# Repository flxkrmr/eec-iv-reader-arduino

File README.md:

# Arduino EEC IV Reader

Arduino implementation of the DCL-Protocol to communicate with Ford EEC-IV ECUs.

Please check out the Wiki for more information.

This is currently a work in progress and not completely working. Use at your own risk!

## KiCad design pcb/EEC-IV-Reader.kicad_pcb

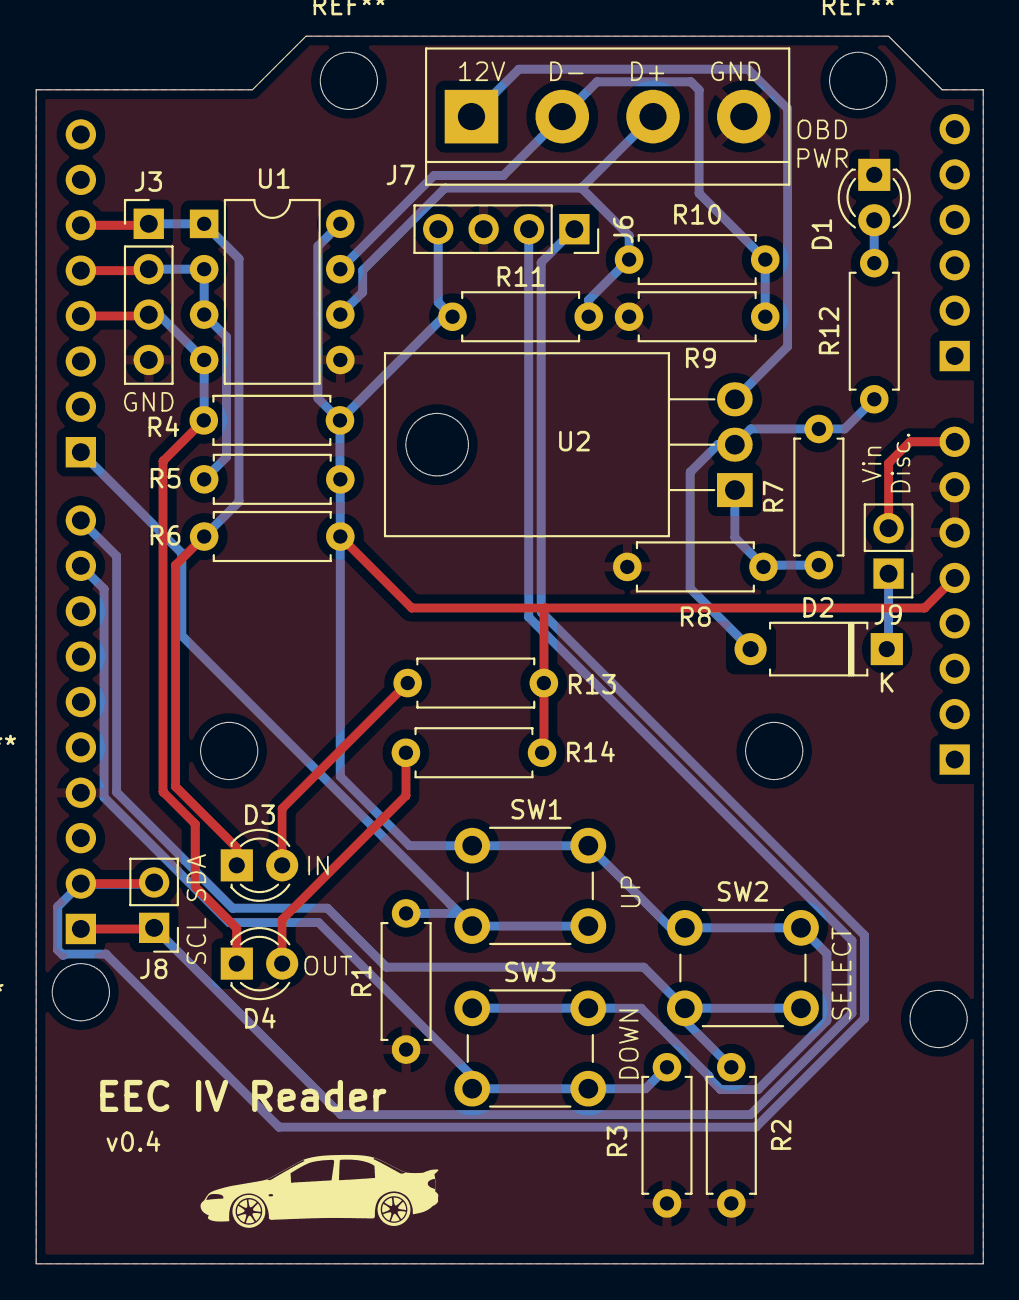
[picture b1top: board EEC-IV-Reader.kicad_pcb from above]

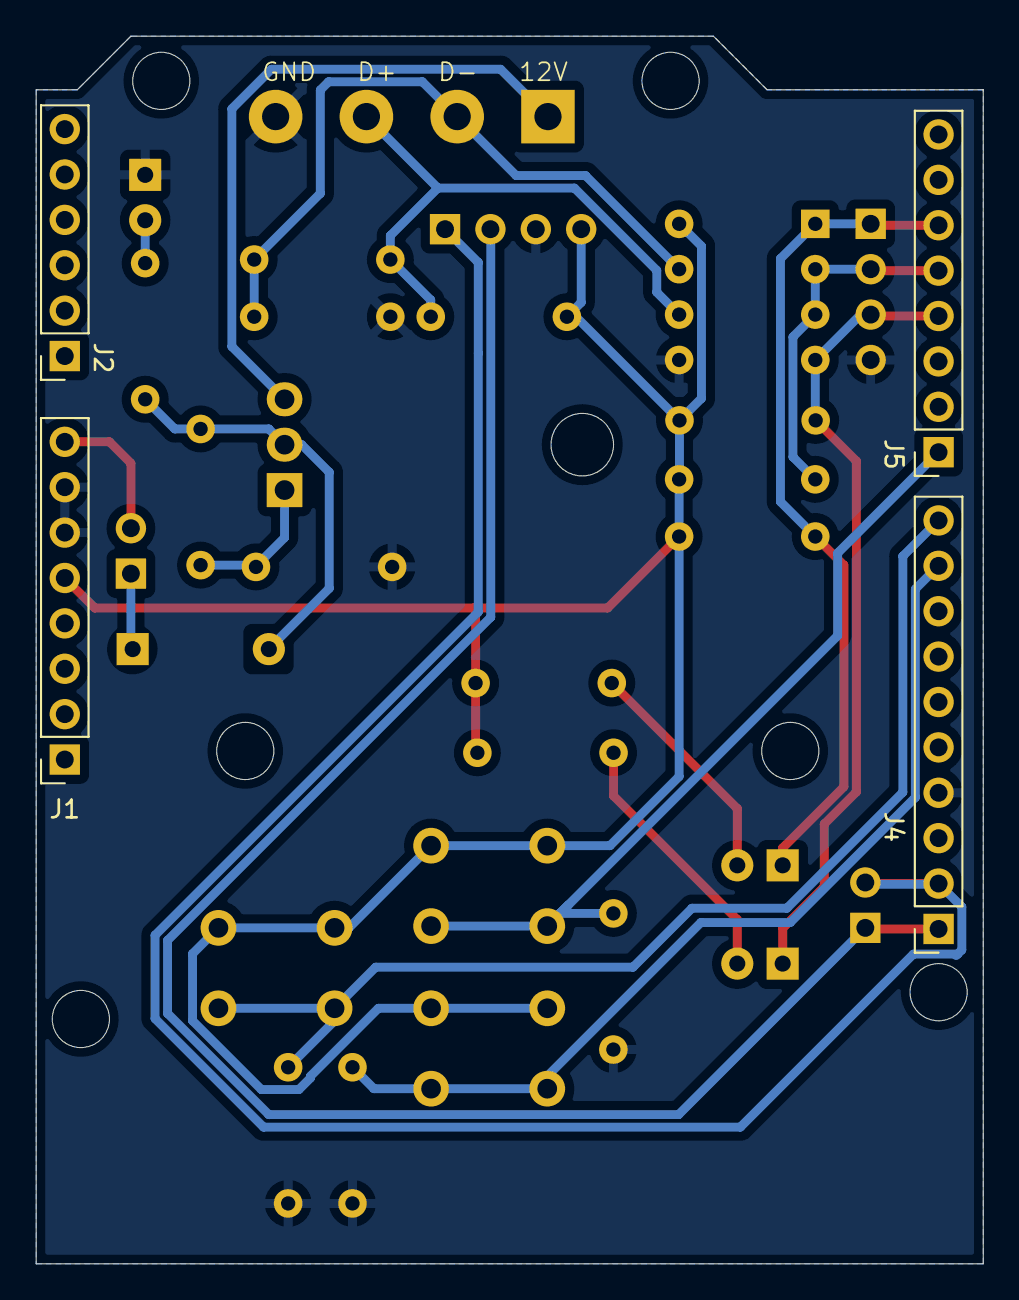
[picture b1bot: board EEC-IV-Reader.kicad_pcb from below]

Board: 2 copper layers, 53.0 x 68.7 mm, 32 parts (4 on the bottom side), 20 nets.

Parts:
D1, D3, D4: LED; LED_D3.0mm
D2: D_Schottky; D_A-405_P7.62mm_Horizontal
J1: ARDUINO_1; PinSocket_1x08_P2.54mm_Vertical
J2: ARDUINO_2; PinSocket_1x06_P2.54mm_Vertical
J3: RS_485_DEBUG; PinHeader_1x04_P2.54mm_Vertical
J4: ARDUINO_3; PinSocket_1x10_P2.54mm_Vertical
J5: ARDUINO_4; PinSocket_1x08_P2.54mm_Vertical
J6: DISPLAY; PinSocket_1x04_P2.54mm_Vertical
J7: OBD; TerminalBlock_bornier-4_P5.08mm
J8: I2C_DEBUG; PinHeader_1x02_P2.54mm_Vertical
J9: Vin_disconnect; PinHeader_1x02_P2.54mm_Vertical
R1, R2, R3, R4, R5, R6: 10k; R_Axial_DIN0207_L6.3mm_D2.5mm_P7.62mm_Horizontal
R7: 240; R_Axial_DIN0207_L6.3mm_D2.5mm_P7.62mm_Horizontal
R8: 1k3; R_Axial_DIN0207_L6.3mm_D2.5mm_P7.62mm_Horizontal
R9, R11: 20k; R_Axial_DIN0207_L6.3mm_D2.5mm_P7.62mm_Horizontal
R10: 120; R_Axial_DIN0207_L6.3mm_D2.5mm_P7.62mm_Horizontal
R12: 300; R_Axial_DIN0207_L6.3mm_D2.5mm_P7.62mm_Horizontal
R13, R14: 160; R_Axial_DIN0207_L6.3mm_D2.5mm_P7.62mm_Horizontal
SW1: BTN_UP; SW_PUSH_6mm_H4.3mm
SW2: BTN_SEL; SW_PUSH_6mm_H4.3mm
SW3: BTN_DOWN; SW_PUSH_6mm_H4.3mm
U1: MAX485E; DIP-8_W7.62mm
U2: LM317_TO-220; TO-220-3_Horizontal_TabDown

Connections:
2: D3.1 (K), J3.1, J5.6, R6.2, U1.1 (RO)
3: J3.2, J5.5, R5.2, U1.2 (~RE), U1.3 (DE)
4: D4.1 (K), J3.3, J5.4, R4.2, U1.4 (DI)
7: J5.1, R1.1, SW1.2
8: J4.10, R2.1, SW2.2
9: J4.9, R3.1, SW3.2
+5V: J1.5, J6.4, R4.1, R5.1, R6.1, R11.2, R13.1, R14.1, SW1.1, SW2.1, SW3.1, U1.8 (VCC)
+12V: J7.1, U2.3 (VI)
/8V: D2.1 (K), R7.1, R12.1, U2.2 (VO)
D+: J7.3, R10.2, R11.1, U1.6 (A)
D-: J7.2, R9.2, R10.1, U1.7 (B)
GND: D1.1 (K), J1.6, J1.7, J3.4, J4.4, J6.3, J7.4, R1.2, R2.2, R3.2, R8.2, R9.1, U1.5 (GND)
unnamed: D1.2 (A), R12.2
unnamed: D2.2 (A), J9.1
unnamed: D3.2 (A), R13.2
unnamed: D4.2 (A), R14.2
unnamed: R7.2, R8.1, U2.1 (ADJ)
SCL: J4.1, J6.2, J8.1
SDA: J4.2, J6.1, J8.2
VIN: J1.8, J9.2

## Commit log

2022-02-03 First working
2022-02-06 Log output for sync logic
2022-02-06 Logging sync message
2022-02-07 Removed docs from repo
2022-02-07 Add sync loop answers
2022-02-07 Move pointer increment
2022-02-07 Add gitignore
2022-02-08 Remove hacked SoftwareSerial
2022-02-10 Fix sync answer timing
2022-02-16 First baud change after sync
2022-02-16 Add state machine
2022-02-16 Somehow reads error code
2022-02-16 Switch fully to SoftwareSerial
2022-02-17 Printing 5 error codes to serial
2022-02-22 Added timeout and starting when sync loop is on
2022-02-22 Add todo list
2022-02-25 Rename all
2022-02-25 Refactor code
2022-02-25 Fix koeo
2022-02-26 Add .docs to gitignore
2022-02-26 Add readme
2022-02-26 Update ui
2022-02-26 Add comments to koeo
2022-03-05 Add button ui
2022-03-06 Move fault code to external class
2022-03-06 Move koeo to external class
2022-03-06 Add live data WIP
2022-03-06 Fix segmentation fault error
2022-03-20 WIP menu
2022-03-21 Add display gui
2022-04-04 Switch back to big class
2022-04-06 Switch to homemade menu
2022-04-06 Add koeo to ui
2022-04-06 Remove live data from ui
2022-04-11 Update TODO
2022-10-07 Add circuit board
2022-10-23 Fix pin out for proto board
2022-10-28 Port to platformio
2022-10-28 Remove submodules and add static files
2022-10-28 Fix git mess
2022-10-28 Invert KOEO menu
2022-10-28 Add basic unit test
2022-10-28 WIP: Implement fault code util with tests
2022-10-29 Implement fault code util with tests
2022-10-29 Fix string assertion
2022-10-29 Add convenience method
2022-10-30 Print readable message on fault code
2022-10-30 Remove usage of readable error codes
    Memory is too low.
2022-10-30 Improve board
2022-11-04 Rename modes
2022-11-04 Add start message timeout
2022-11-04 Get out of static message with up and down button
2022-11-06 Cleanup files
2022-12-30 Update PCB
2023-01-08 Stop on koeo code 000
2023-01-13 Update LED Labels and Diode direction
2023-01-13 Fix koeo for dynamic error number
2023-01-14 Fixing koeo again for only one error
2023-01-14 Add comments on koeo variables
2023-01-14 Add version
2023-01-20 Add terminal labels to backside
2023-01-20 Add bom
2023-01-20 Fix version
2023-01-20 Fix footprint
2023-01-20 Add step file
2023-01-20 Remove unused classes
2023-01-20 Improve variable size
2023-01-20 Increase version
2023-01-21 Memory improvement and warning cleanup
2023-01-26 Use OneButton Library
2023-01-26 Fix button setup
2023-01-26 Remove wire library
2023-01-26 Add small memory improvements
2023-01-27 Fix warning
2023-01-27 Add voltage divider to measure battery voltage
2023-01-27 Add voltage measurement
2023-01-27 Fix resistor value
2023-01-29 Add softwareSerial fork
2023-01-29 Remove SoftwareSerial Fork
2023-01-31 Revert "Delete clearing of DCL Error Flag Registers"
    This reverts commit 4e58cb0d945757c14b122edca00dc5dcedb48b1c.
2023-02-01 Simplify sync and only listen to index value
    Only consider the last byte of each sync frame
2023-02-02 Improve output
2023-02-02 Remove warnings
2023-02-11 Add CART abstraction. Not yet fully working
2023-02-11 Fault code WIP
2023-02-12 Fault code working with CART class
2023-02-12 Refactoring
2023-02-17 Add CART reset() and frameDone
2023-02-17 Fix double koeo code
2023-02-17 Bump version
2023-02-17 Add id slot parity check
2023-02-19 Test shorter start message
2023-02-19 Read DCL Error flags
2023-02-19 Fix bugs
2023-02-21 Wait for self test done flag
2023-02-21 Use error collecting logic for both tests
2023-02-22 Added hardware folder for different calibrations
    Including disassembly of SEAL catch code, initial commit, not finished
2023-02-22 Adding FORD documentation for CART/UART
2023-02-23 Shrink start message to 11 bytes
2023-02-23 Remove voltage monitor with define
2023-02-23 Start with live data
2023-02-23 Add firmware update script for windows
2023-02-23 Update gitignore for firmware update
2023-02-24 Allow cart to read multiple IWs in data slot
2023-02-24 Improve collection of fault codes
2023-02-24 Remove log
2023-02-24 This was right before
2023-02-26 Update gitignore
2023-03-02 Add live data
2023-03-02 Remove buffer reset
2023-03-02 Remove unused functions
2023-03-02 Remove voltage reader as live data can do this
2023-03-02 Fix multiple code bug
2023-03-02 Add curses lib to gui
2023-03-03 Update gui
2023-03-03 Add com menu to app
2023-03-17 Remove simple gui
2023-03-17 Improve GUI communication
2023-03-17 Use other live data pids
2023-03-20 Fix sync bug when engine is running
2023-03-24 Send more pids
2023-03-25 Try more pids
2023-03-25 Create PID checksums on the fly
2023-03-26 Send big live data chunk
2023-03-26 Output live data serial in chunks
